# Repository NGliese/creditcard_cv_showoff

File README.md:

This Dockerfile installs the ESP-IDF dependencies, installs the python3-venv package, clones the ESP-IDF repository, sets the environment variables, sets the working directory to /app, copies the project files into the container, and builds the project using idf.py.

# Prerequisites
1) install docker
It is recommended to install Docker using the convenience script. See the detailed instructions for the installation on the Docker website:
    https://docs.docker.com/engine/install/ubuntu/#install-using-the-convenience-script

    Tip: preview script steps before running

    You can run the script with the --dry-run option to learn what steps the script will run when invoked:

    $ curl -fsSL https://get.docker.com -o get-docker.sh
    $ sudo sh ./get-docker.sh --dry-run

    To install the script, after reviewing, run the script without the --dry-run option:
    $ curl -fsSL https://get.docker.com -o get-docker.sh
    $ sudo sh ./get-docker.sh

2) install git

To use this Dockerfile, create a new directory for your ESP32 project and copy the Dockerfile into it. Then, copy your project files into the same directory and run the following command to build the Docker image:

docker build -t esp32_plc_mock2 .

Replace esp32_plc_mock2 with the name you want to give your Docker image.

Once the Docker image is built, you can run the following command to start a new container and build your project:

docker run -it --device=/dev/ttyUSB0 -v $(pwd):/app esp32_plc_mock2

This command starts a new container with the esp32_plc_mock2 image, mounts the current directory ($(pwd)) as a volume inside the container, and sets the working directory to /app. You can then run idf.py commands inside the container to build and flash your project.

# see the makefile for more details

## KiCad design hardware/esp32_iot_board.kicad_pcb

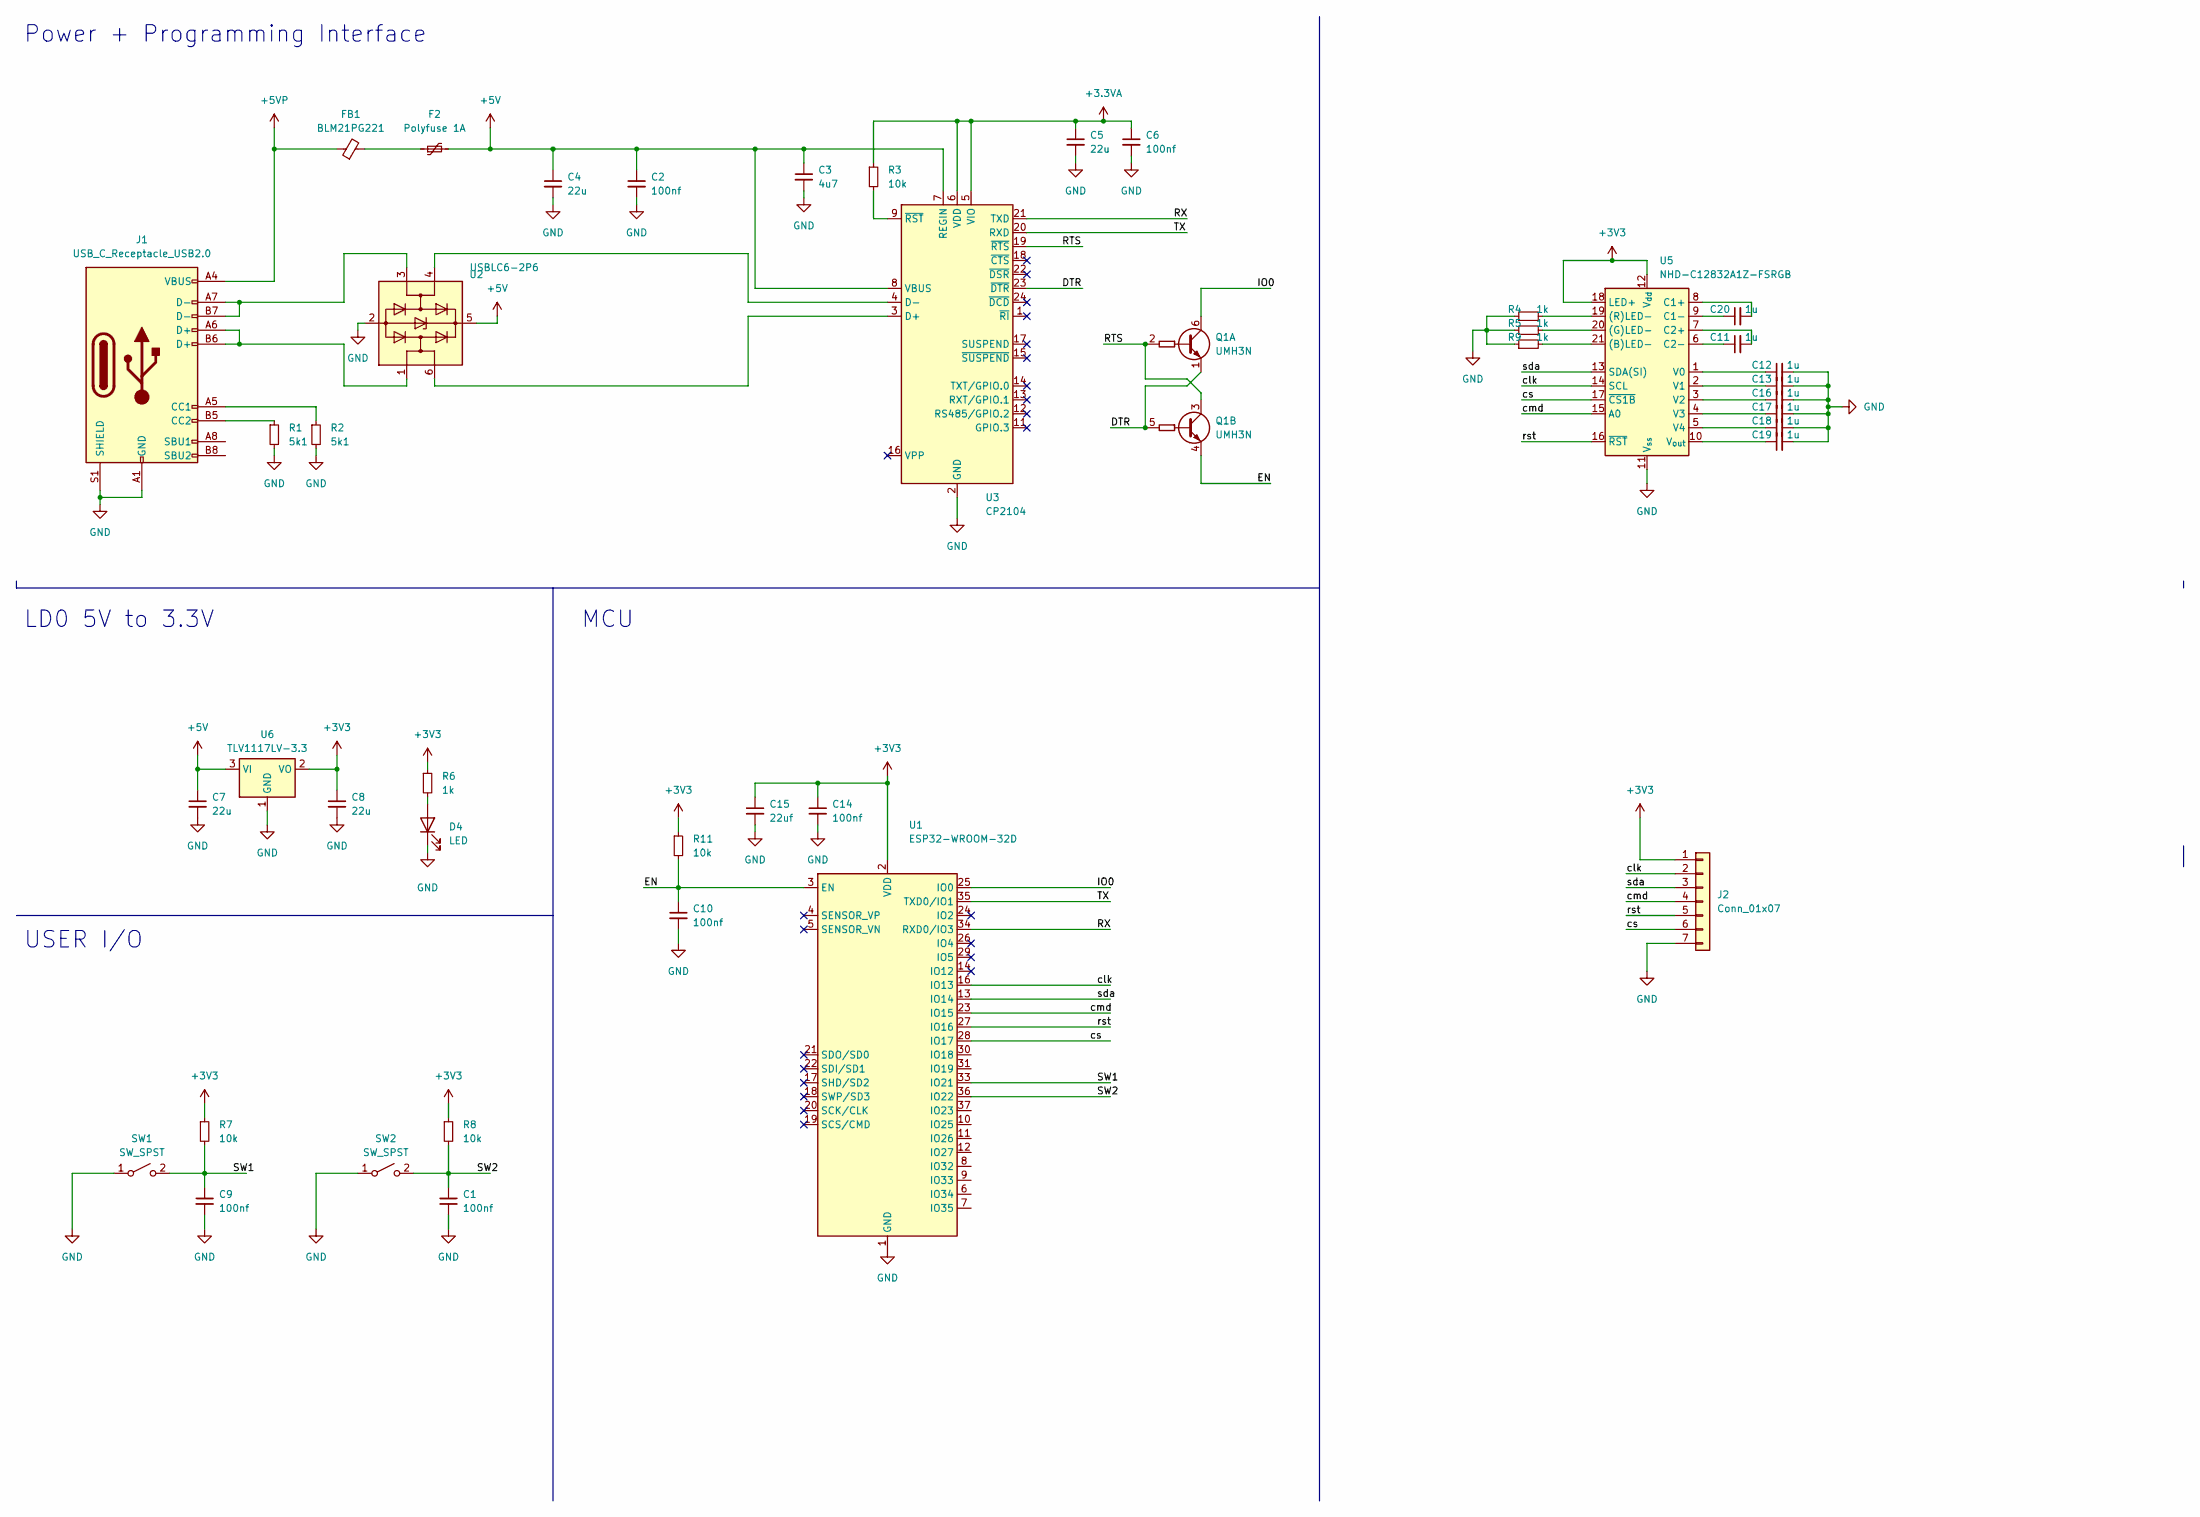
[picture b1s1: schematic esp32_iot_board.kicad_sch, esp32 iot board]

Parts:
C1, C2, C6, C9, C10, C14: 100nf; C_1206_3216Metric; LCSC C77502
C3: 4u7; C_1206_3216Metric; LCSC C91602
C4, C5, C7, C8: 22u; C_1206_3216Metric; LCSC C304004
C11, C12, C13, C16, C17, C18, C19, C20: 1u; C_0603_1608Metric; LCSC C559292
C15: 22uf; C_1206_3216Metric; LCSC C304004
D4: LED; LED_1206_3216Metric
F2: Polyfuse 1A; Fuse_1206_3216Metric_Pad1.42x1.75mm_HandSolder; LCSC C66453
FB1: BLM21PG221; L_0603_1608Metric_Pad1.05x0.95mm_HandSolder; LCSC C85840
J1: USB_C_Receptacle_USB2.0; USB_C_Receptacle_HRO_TYPE-C-31-M-12; LCSC C2760486
J2: Conn_01x07; PinHeader_1x07_P2.54mm_Vertical
Q1: UMH3N; SOT-363_SC-70-6; LCSC C62892
R1, R2: 5k1; R_1206_3216Metric; LCSC C212533
R3: 10k; R_0603_1608Metric; LCSC C384294
R4, R5, R6, R9: 1k; R_1206_3216Metric; LCSC C131398
R7, R8, R11: 10k; R_1206_3216Metric; LCSC C118075
SW1, SW2: SW_SPST; SW_Push_1P1T_NO_6x6mm_H9.5mm; LCSC C221869
U1: ESP32-WROOM-32D; LCSC C473012
U2: USBLC6-2P6; SOT-666; LCSC C2827693
U3: CP2104; QFN-24-1EP_4x4mm_P0.5mm_EP2.6x2.6mm; LCSC C47742
U5: NHD-C12832A1Z-FSRGB
U6: TLV1117LV-3.3; SOT-223-3_TabPin2; LCSC C15578

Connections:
+3.3VA: C5.1, C6.1, R3.1, U3.5 (VIO), U3.6 (VDD)
+3V3: C8.1, C14.1, C15.1, J2.1, R6.1, R7.1, R8.1, R11.1, U1.2 (VDD), U5.12 (V_{dd}), U5.18 (LED+), U6.2 (VO)
+5V: C2.1, C3.1, C4.1, C7.1, F2.2, U2.5 (VBUS), U3.7 (REGIN), U3.8 (VBUS), U6.3 (VI)
+5VP: FB1.1, J1.A4 (VBUS), J1.A9 (VBUS), J1.B4 (VBUS), J1.B9 (VBUS)
/DTR: Q1.1 (E1), Q1.5 (B2), U3.23 (~DTR)
/EN: C10.1, Q1.4 (E2), R11.2, U1.3 (EN)
/IO0: Q1.6 (C1), U1.25 (IO0)
/RTS: Q1.2 (B1), Q1.3 (C2), U3.19 (~RTS)
/RX: U1.34 (RXD0/IO3), U3.21 (TXD)
/SW1: C9.1, R7.2, SW1.2 (B), U1.33 (IO21)
/SW2: C1.1, R8.2, SW2.2 (B), U1.36 (IO22)
/TX: U1.35 (TXD0/IO1), U3.20 (RXD)
/clk: J2.2, U1.16 (IO13), U5.14 (SCL)
/cmd: J2.4, U1.23 (IO15), U5.15 (A0)
/cs: J2.6, U1.28 (IO17), U5.17 (~CS1B)
/rst: J2.5, U1.27 (IO16), U5.16 (~RST)
/sda: J2.3, U1.13 (IO14), U5.13 (SDA(SI))
GND: C1.2, C2.2, C3.2, C4.2, C5.2, C6.2, C7.2, C8.2, C9.2, C10.2, C12.2, C13.2, C14.2, C15.2, C16.2, C17.2, C18.2, C19.2, D4.1 (K), J1.A1 (GND), J1.A12 (GND), J1.B1 (GND), J1.B12 (GND), J1.S1 (SHIELD), J2.7, R1.2, R2.2, R4.1, R5.1, R9.1, SW1.1 (A), SW2.1 (A), U1.1 (GND), U1.15 (GND), U1.38 (GND), U1.39 (GND), U2.2 (GND), U3.2 (GND), U3.25 (GND), U5.11 (V_{ss}), U6.1 (GND)
unnamed: D4.2 (A), R6.2
unnamed: F2.1, FB1.2
unnamed: J1.A5 (CC1), R2.1
unnamed: J1.B5 (CC2), R1.1
unnamed: J1.A6 (D+), J1.B6 (D+), U2.1 (I/O1)
unnamed: J1.A7 (D-), J1.B7 (D-), U2.3 (I/O2)
unnamed: U2.6 (I/O1), U3.3 (D+)
unnamed: U2.4 (I/O2), U3.4 (D-)
unnamed: R3.2, U3.9 (~RST)
unnamed: R9.2, U5.21 ((B)LED-)
unnamed: R5.2, U5.20 ((G)LED-)
unnamed: R4.2, U5.19 ((R)LED-)
unnamed: C20.2, U5.8 (C1+)
unnamed: C20.1, U5.9 (C1-)
unnamed: C11.2, U5.7 (C2+)
unnamed: C11.1, U5.6 (C2-)
unnamed: C12.1, U5.1 (V0)
unnamed: C13.1, U5.2 (V1)
unnamed: C16.1, U5.3 (V2)
unnamed: C17.1, U5.4 (V3)
unnamed: C18.1, U5.5 (V4)
unnamed: C19.1, U5.10 (V_{out})

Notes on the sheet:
LD0 5V to 3.3V
Power + Programming Interface
MCU
USER I/O

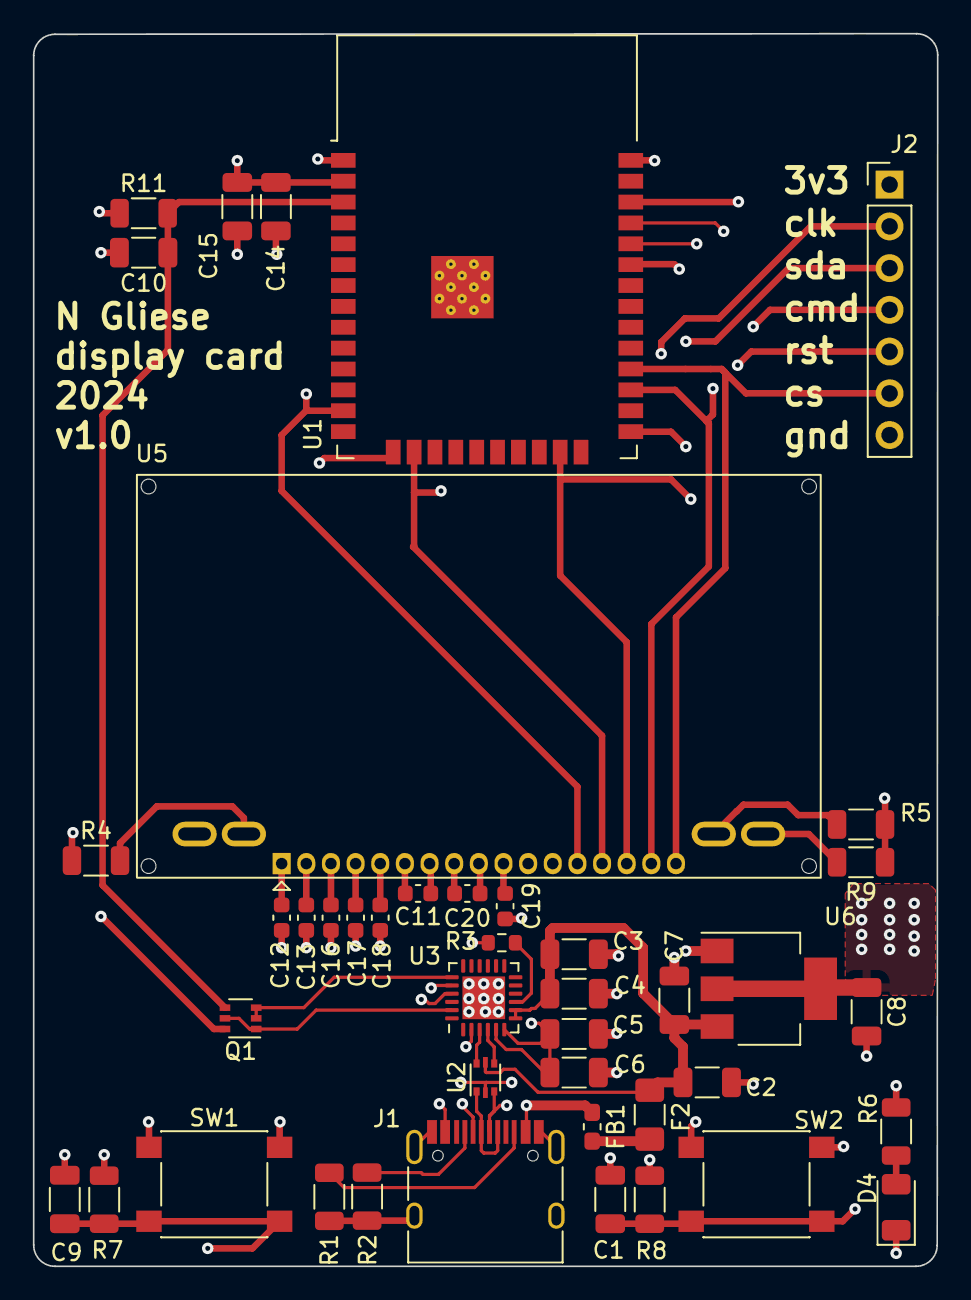
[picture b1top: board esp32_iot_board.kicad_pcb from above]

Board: 4 copper layers, 55.0 x 75.0 mm, 43 parts (0 on the bottom side), 40 nets.

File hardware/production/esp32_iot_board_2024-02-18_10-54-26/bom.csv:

Designator,Footprint,Quantity,Value,LCSC Part #
"C1, C10, C14, C2, C6, C9",1206,6,100nf,C77502
"C11, C12, C13, C16, C17, C18, C19, C20",0603,8,1u,C559292
C15,1206,1,22uf,C304004
C3,1206,1,4u7,C91602
"C4, C5, C7, C8",1206,4,22u,C304004
D4,1206,1,LED,
F2,1206,1,Polyfuse 1A,C66453
FB1,0603,1,BLM21PG221,C85840
J1,USB_C_Receptacle_HRO_TYPE-C-31-M-12,1,USB_C_Receptacle_USB2.0,C2760486
J2,PinHeader_1x07_P2.54mm_Vertical,1,Conn_01x07,
Q1,SOT-363_SC-70-6,1,UMH3N,C62892
"R1, R2",1206,2,5k1,C212533
"R11, R7, R8",1206,3,10k,C118075
R3,0603,1,10k,C384294
"R4, R5, R6, R9",1206,4,1k,C131398
"SW1, SW2",SW_Push_1P1T_NO_6x6mm_H9.5mm,2,SW_SPST,C221869
U1,ESP32-WROOM-32D,1,ESP32-WROOM-32D,C473012
U2,SOT-666,1,USBLC6-2P6,C2827693
U3,QFN-24-1EP_4x4mm_P0.5mm_EP2.6x2.6mm,1,CP2104,C47742
U5,NHD-C12832A1Z-FSRGB,1,NHD-C12832A1Z-FSRGB,
U6,SOT-223-3_TabPin2,1,TLV1117LV-3.3,C15578

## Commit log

2024-02-19 hardware init
2024-02-19 setup googletest and cleared unused code
2024-02-20 added unit test with code cov
2024-02-25 included button with isr
2024-03-12 added tests to lcd gpio and timer
2024-04-08 init hello world to lcd success
2024-04-08 finished
